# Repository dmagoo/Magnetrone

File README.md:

# Magnetrone

A motorized MIDI sequencer built around a rotating platter driven by a stepper motor.
Magnets placed on the platter pass over Hall effect sensors to trigger MIDI notes,
turning physical arrangement into musical pattern.

---

## Features

- Rotating platter driven by NEMA17 stepper via GT2 belt drive (11:1)
- 8 analog Hall effect sensors, one per note in the current scale
- MIDI note output on DIN connector
- Teensy Audio Shield output (headphone/line out) with a built-in synth and drum kit
- Voices: Piano, E. Piano, Organ, Synth, Bass, Strings, Brass, Mallets, Reed, Guitar
  and Drums, each with its own wave or harmonics, envelope, note length and filter,
  plus None to mute a layer
- Voice Edit (Aux): live tweaks to a layer's wave, envelope and note length,
  its first 16 harmonics, and its own filter with a filter envelope; Save As keeps them in Custom 1-8 (shared by all
  scenes) or as the current scene's own Scene Voice
- Edit Scale: a Custom scale with one chosen note per track, from Sound
  Defaults or live on the Aux; Save As keeps it in Custom 1-8 (shared by all
  scenes)
- Two magnet layers: a magnet's normal pole plays Layer A, its reversed pole Layer B
  (or both, with Layer B's Mode on Stack, or taking turns by revolution, with
  Layer Turns on Alternate, or each on its own Edit Turns pattern of up to 8
  revolutions),
  each with its own voice, MIDI channel, root note, scale, octave, level, Track
  Shift, Wrap and Low Note (Layer B can follow A's voice, octave, root, scale,
  shift and Low Note one by one, from the menu or the Aux; octave, root and
  scale follow by default)
- Per-layer effects, in a fixed chain: Tone (low-pass Cutoff and Resonance),
  Chorus (Rate, Depth, Mix), Delay (Sync to the beat or Free in ms, up to
  2.4 s, Feedback up to 90%, Mix) and Reverb (Room Size, Damping, Mix). Saved
  in scenes, all off by default; Layer B can follow A's per effect. Tone
  Cutoff, Delay Mix, Delay Feedback and Reverb Mix are also Aux Fns
- Per-layer Track Shift raises the run by scale degrees, with Wrap (the run
  rotates around the arm) or No Wrap (the whole run transposes)
- Per-layer Low Note: Inner or Outer sets which end of the sensor arm plays
  the low end of the run
- Drums play a fixed GM kit (one drum per track, busiest on the outer tracks) on
  MIDI channel 10; Track Shift rotates the kit around the tracks and Low Note
  Outer flips it end to end
- 1 revolution = 1 bar; BPM tracks RPM automatically. Beats/Rev from 1 to 32,
  platter speed from 1 to 120 RPM
- The platter is marked in 16 steps
- Bar start (StartPos): a start mark on the platter, located by calibration or
  re-found later (Auto from one magnet, or Manual by jogging the platter), and
  remembered across power cycles when the platter was at rest
- Front: where the player sits, set first in calibration and Calib. StartPos
  (the magnet is turned to the player, by hand or with the Speed knob, before
  the spin). Tools > Go to Front turns the mark there the shorter way round
- Placement Mode (Tools): Speed jogs the platter (press: Go to Front), Aux snaps
  to the next step or beat, Volume mutes and unmutes single tracks
- Scenes: the whole sound of both layers, 8 saved slots plus a Defaults scene
  edited from the menu; loaded live on the next bar start (or at once, Play
  Setup > Scene Load). Aux changes are live
  only, on top of the current scene. Read-only demo scenes are built into the
  firmware from JSON files (docs/scene-format.md), and a `scenes` serial
  command prints the saved scenes in that format
- Scene Codes (Aux > Scene Codes): a code of up to 14 characters for the
  current sound's main settings (each layer's root, octave, scale, voice,
  shift, Low Note, Wrap and mode, plus Layer Turns and the turn patterns), to enter on another
  table or after a firmware update. Fields at their defaults cost nothing, so
  a code changing only the roots is 3 characters
- [Record Designer](https://dmagoo.github.io/Magnetrone/tools/record-designer/) (`tools/record-designer/`): a
  browser tool to design a "record", a magnet pattern on a step grid plus its
  Scene Code, play it back, save songs and share them as links, and export a
  full-size SVG/PDF template to print or laser cut into a platter cover. Runs
  from the link or straight from disk
- MIDI beat clock driven by platter position, with Song Position Pointer so
  external bars line up with the start mark
- MIDI in (control only): a per-layer input channel; keys drive a MIDI Fn
  (Pitch, Shift, Scale Learn, Set Scale, Fingered or One Finger), the bend wheel bends the table, CC 7 volume,
  CC 20 octave; with Play Setup > MIDI CC on, CCs 74, 71, 93, 94, 12 and 91
  set the effects
- LCD menu: Sound Defaults (both layers), Play Setup, System and Tools
- Speed and volume adjustable live at any time via dedicated encoders; touching
  either one returns to the home screen from any menu (prompts and Scene
  Code entry excepted).
  From a stop, turning Speed starts from zero in the turned direction; a
  press resumes the last speed
- Aux knob changes one bound function live (Pitch, A/B Balance, Layer Turns, Load Scene,
  or a layer's Voice, Root Note, Scale, Octave, Shift, Low Note, Wrap, Mode,
  Tone Cutoff, Delay Mix, Delay Feedback or Reverb Mix); its list also holds
  Save Scene, Scene Codes and Reset All
- Menu knob opens the main menu from the home screen by turning or pressing;
  the Menu button leaves the Aux screens straight back to the home screen, and
  the Aux button leaves the main menu (prompts excepted)
- Welcome tune plays on boot -- previews what Layer A's tracks play, hall 1 to 8
  and back, including its key, octave, Track Shift, Wrap and Low Note; a Menu
  button press skips it
- LCD backlight timeout: configurable from always off to always on
- Stepper motor sleeps when idle to reduce heat and power draw
- Calibration (at 24 RPM, clear platter then one magnet on the start mark)
  measures sensor baselines and noise, threshold, magnet pole, the belt reduction
  (e.g. "Belt 10.9:1", counted in motor steps) and the bar start
- Tools menu: Go to StartPos, Go to Front, Placement Mode, calibration,
  StartPos, Machine Info (RPM, belt ratio, StartPos, threshold, motor driver), live
  Sensor Levels, Sensor Timing, Track Notes and Resources (audio load) screens, Reset Settings (keeps calibration, Front and scenes
  1-8) and Factory Reset
- All settings persisted to EEPROM across power cycles
- Teensy 4.1

---

## Code Summary

The firmware is structured as a set of independent modules: stepper motor control
uses an IntervalTimer ISR for non-blocking step generation; Hall sensor polling
fires each note when the magnet is centered on its sensor, predicted from a
threshold-to-peak angle each sensor learns as it plays (so timing holds on every
track and at any speed), with re-arm and debounce; the sequencer maps sensor
index to scale degree and fires timed MIDI note on/off pairs; the audio module drives
an 8-voice synth bank per magnet layer plus a shared drum kit through the SGTL5000
codec in parallel with MIDI out; the menu
is a simple state machine driven by three encoders with live speed and volume handling
at all times. The platter keeps a signed step count, so the bar phase is exact; MIDI
clock and scene loads are driven from it. A calibration routine samples the sensor
baselines and noise, counts motor steps over one platter revolution, and derives a threshold,
RPM correction factor and bar start stored in EEPROM.

---

## Hardware Summary

The controller is built on a Teensy 4.1 with a Teensy Audio Shield (SGTL5000) for
audio output. A NEMA17 stepper motor drives the platter through a GT2 belt at 11:1
reduction, controlled by a TMC2209 driver (configured over UART) from 24V DC. Eight
ratiometric Hall effect sensors (A1301) are powered at 3.3V and read directly by the
Teensy ADC. A 16x2 I2C LCD with PCF8574T backpack provides the display. MIDI DIN
in/out is present with optoisolation on the input. Power is supplied via 24V barrel
jack through a panel-mount power switch and an MP1584EN buck converter to 5V.

---

## Installation

### Requirements

- PlatformIO (CLI or VS Code extension)
- Teensy 4.1

### Build and Upload

1. Open the `firmware/` directory in VS Code with the PlatformIO extension,
   or use the PlatformIO CLI.

2. Build:

       cd firmware
       pio run -e teensy41

3. Upload:

       pio run -e teensy41 --target upload

### First Run

On first boot, no calibration data is present and the table offers to calibrate
(later: Menu > Tools > Full Calibrate). Clear the platter when asked, then place a
single magnet on the start mark on the outer track. See the
[user guide](docs/user-guide.md) for details.

### Diagnostics

For hardware faults, the firmware has a diagnostics mode used over the USB
serial monitor (`pio device monitor`). Hold the Menu button at power-up, or
type `diag` in the monitor while the table runs. It reports the display, audio
board, motor driver and every sensor every 5 seconds, and takes commands for
running and tuning the motor. Type `help` in the monitor for the commands; see
Troubleshooting > Diagnostics mode in the [user guide](docs/user-guide.md).

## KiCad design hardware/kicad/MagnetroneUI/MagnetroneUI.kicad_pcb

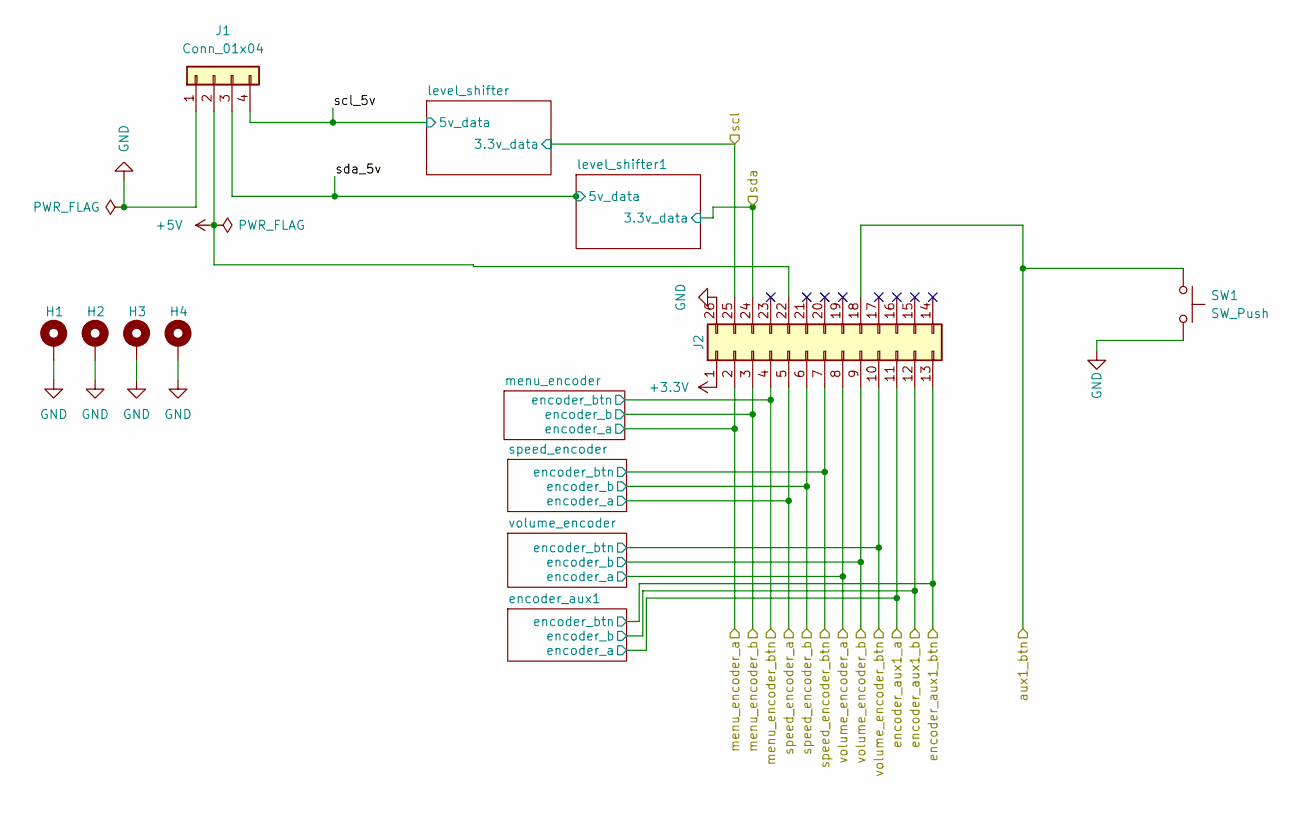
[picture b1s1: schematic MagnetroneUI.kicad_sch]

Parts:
H1, H2, H3, H4: MountingHole_Pad; MountingHole_3.2mm_M3_ISO7380_Pad_TopBottom
J1: Conn_01x04; PinHeader_1x04_P2.54mm_Vertical
J2: Conn_02x13_Counter_Clockwise; IDC-Header_2x13_P2.54mm_Horizontal
SW1: SW_Push; TerminalBlock_Phoenix_MKDS-1,5-2_1x02_P5.00mm_Horizontal

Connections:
+3.3V: J2.1; also elsewhere on the board
+5V: J1.2, J2.22; also elsewhere on the board
/aux1_btn: J2.18, SW1.1
/encoder_aux1_a: J2.11; also elsewhere on the board
/encoder_aux1_b: J2.12; also elsewhere on the board
/encoder_aux1_btn: J2.13; also elsewhere on the board
/menu_encoder_a: J2.2; also elsewhere on the board
/menu_encoder_b: J2.3; also elsewhere on the board
/menu_encoder_btn: J2.4; also elsewhere on the board
/scl: J2.25; also elsewhere on the board
/scl_5v: J1.4; also elsewhere on the board
/sda: J2.24; also elsewhere on the board
/sda_5v: J1.3; also elsewhere on the board
/speed_encoder_a: J2.5; also elsewhere on the board
/speed_encoder_b: J2.6; also elsewhere on the board
/speed_encoder_btn: J2.7; also elsewhere on the board
/volume_encoder_a: J2.8; also elsewhere on the board
/volume_encoder_b: J2.9; also elsewhere on the board
/volume_encoder_btn: J2.10; also elsewhere on the board
GND: H1.1, H2.1, H3.1, H4.1, J1.1, J2.26, SW1.2; also elsewhere on the board

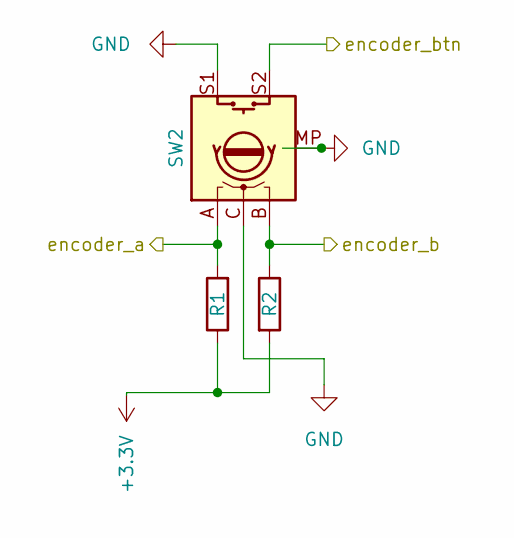
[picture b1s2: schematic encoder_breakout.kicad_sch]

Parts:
R1, R2: 10k; R_0805_2012Metric_Pad1.20x1.40mm_HandSolder
SW2: RotaryEncoder_Switch_MP; RotaryEncoder_Alps_EC11E-Switch_Vertical_H20mm

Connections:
+3.3V: R1.1, R2.2; also elsewhere on the board
/menu_encoder_a: R1.2, SW2.A; also elsewhere on the board
/menu_encoder_b: R2.1, SW2.B; also elsewhere on the board
/menu_encoder_btn: SW2.S2; also elsewhere on the board
GND: SW2.C, SW2.MP, SW2.S1; also elsewhere on the board

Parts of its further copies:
R3, R4, R5, R6, R7, R8: 10k; R_0805_2012Metric_Pad1.20x1.40mm_HandSolder
SW3, SW4, SW5: RotaryEncoder_Switch_MP; RotaryEncoder_Alps_EC11E-Switch_Vertical_H20mm

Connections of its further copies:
+3.3V: R3.1, R4.2, R5.1, R6.2, R7.1, R8.2; also elsewhere on the board
/encoder_aux1_a: R7.2, SW5.A; also elsewhere on the board
/encoder_aux1_b: R8.1, SW5.B; also elsewhere on the board
/encoder_aux1_btn: SW5.S2; also elsewhere on the board
/speed_encoder_a: R3.2, SW3.A; also elsewhere on the board
/speed_encoder_b: R4.1, SW3.B; also elsewhere on the board
/speed_encoder_btn: SW3.S2; also elsewhere on the board
/volume_encoder_a: R5.2, SW4.A; also elsewhere on the board
/volume_encoder_b: R6.1, SW4.B; also elsewhere on the board
/volume_encoder_btn: SW4.S2; also elsewhere on the board
GND: SW3.C, SW3.MP, SW3.S1, SW4.C, SW4.MP, SW4.S1, SW5.C, SW5.MP, SW5.S1; also elsewhere on the board

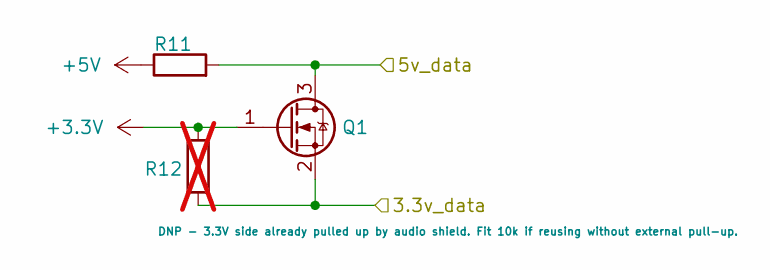
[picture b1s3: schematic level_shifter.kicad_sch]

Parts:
Q1: BSS138; SOT-23
R11: 10k; R_0805_2012Metric_Pad1.20x1.40mm_HandSolder
R12: 10k; R_0805_2012Metric_Pad1.20x1.40mm_HandSolder; not fitted

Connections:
+3.3V: Q1.1 (G), R12.1; also elsewhere on the board
+5V: R11.1; also elsewhere on the board
/scl: Q1.2 (S), R12.2; also elsewhere on the board
/scl_5v: Q1.3 (D), R11.2; also elsewhere on the board

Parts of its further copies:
Q2: BSS138; SOT-23
R13: 10k; R_0805_2012Metric_Pad1.20x1.40mm_HandSolder
R14: 10k; R_0805_2012Metric_Pad1.20x1.40mm_HandSolder; not fitted

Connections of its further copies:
+3.3V: Q2.1 (G), R14.1; also elsewhere on the board
+5V: R13.1; also elsewhere on the board
/sda: Q2.2 (S), R14.2; also elsewhere on the board
/sda_5v: Q2.3 (D), R13.2; also elsewhere on the board

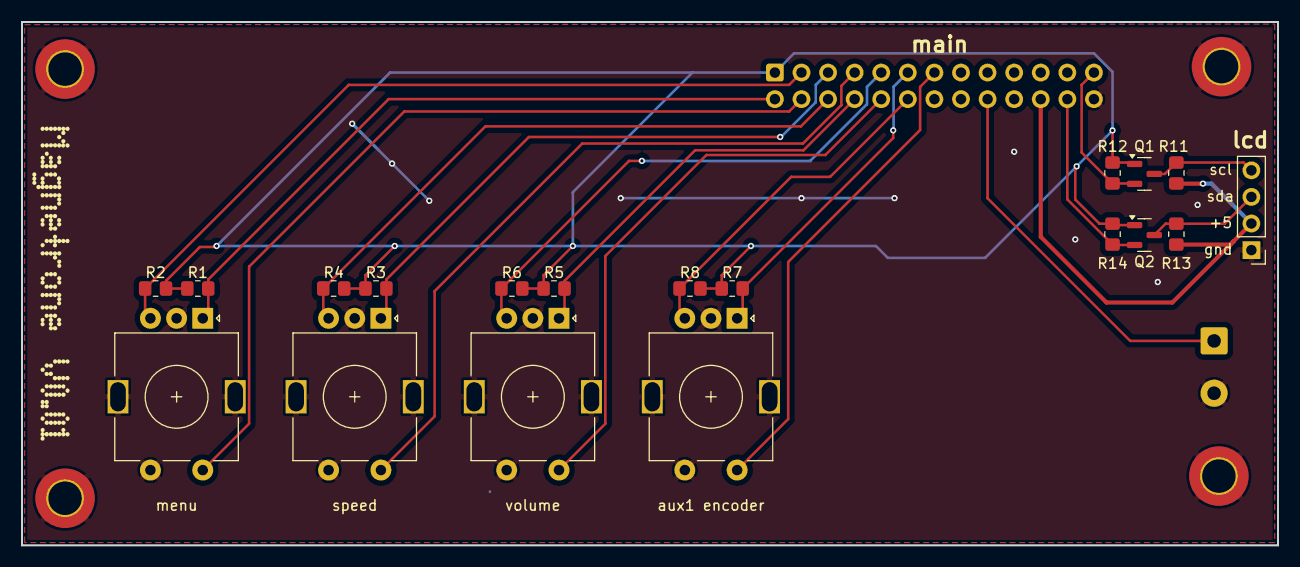
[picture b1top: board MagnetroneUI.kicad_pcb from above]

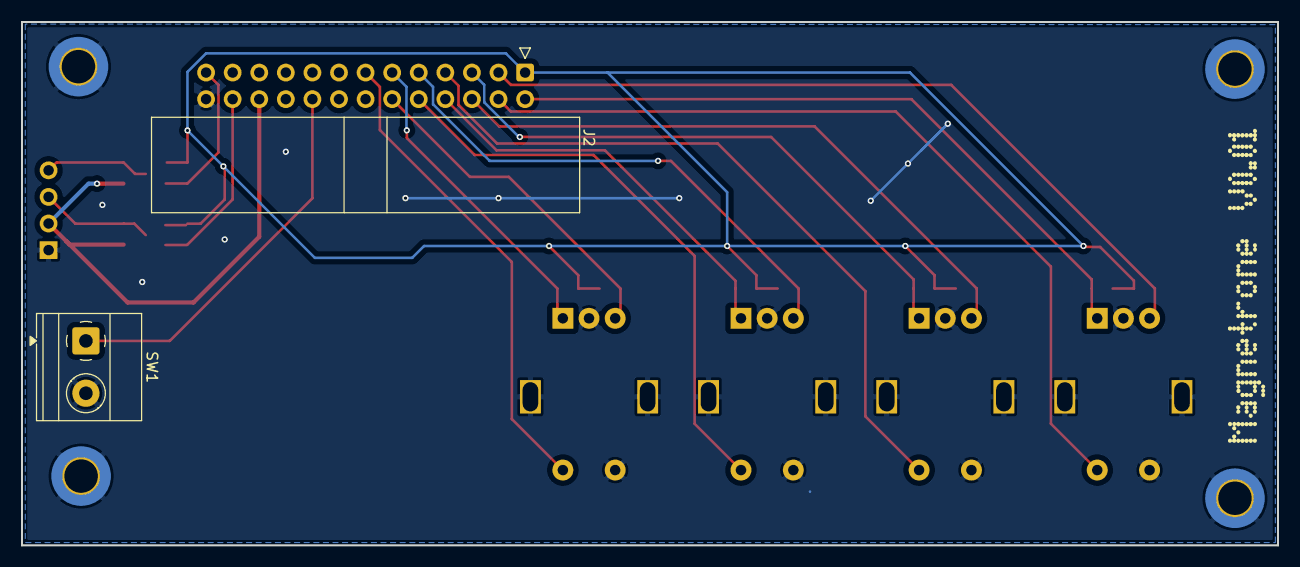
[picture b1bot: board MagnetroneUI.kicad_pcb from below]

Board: 2 copper layers, 120.0 x 50.0 mm, 25 parts (2 on the bottom side), 20 nets.

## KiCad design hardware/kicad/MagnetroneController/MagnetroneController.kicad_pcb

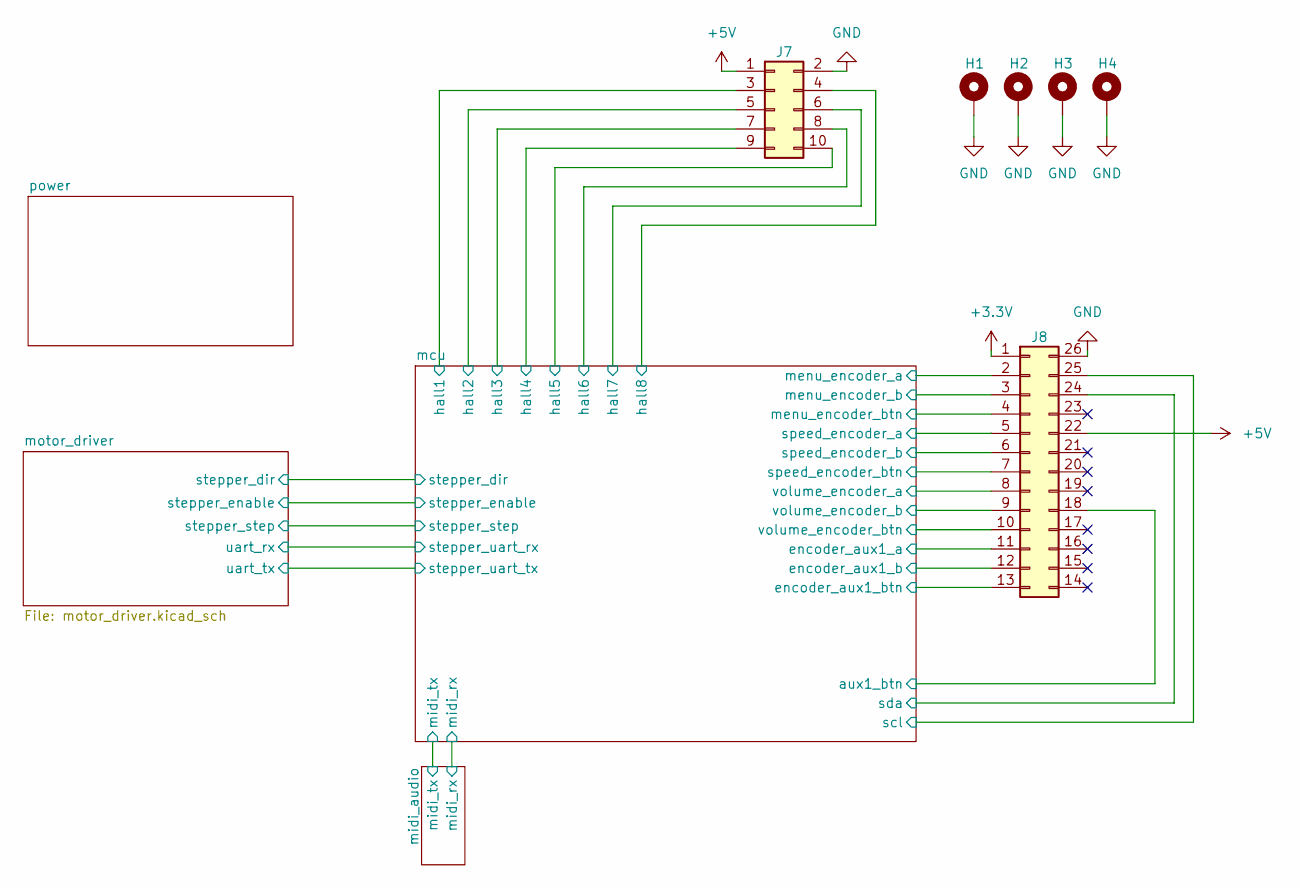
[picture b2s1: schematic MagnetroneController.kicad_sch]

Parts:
H1, H2, H3, H4: MountingHole_Pad; MountingHole_3.2mm_M3_ISO7380_Pad_TopBottom
J7: Conn_02x05_Odd_Even; IDC-Header_2x05_P2.54mm_Vertical
J8: Conn_02x13_Counter_Clockwise; IDC-Header_2x13_P2.54mm_Vertical

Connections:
+3.3V: J8.1; also elsewhere on the board
+5V: J7.1, J8.22; also elsewhere on the board
/mcu/aux1_btn: J8.18; also elsewhere on the board
/mcu/encoder_aux1_a: J8.11; also elsewhere on the board
/mcu/encoder_aux1_b: J8.12; also elsewhere on the board
/mcu/encoder_aux1_btn: J8.13; also elsewhere on the board
/mcu/hall1: J7.3; also elsewhere on the board
/mcu/hall2: J7.5; also elsewhere on the board
/mcu/hall3: J7.7; also elsewhere on the board
/mcu/hall4: J7.9; also elsewhere on the board
/mcu/hall5: J7.10; also elsewhere on the board
/mcu/hall6: J7.8; also elsewhere on the board
/mcu/hall7: J7.6; also elsewhere on the board
/mcu/hall8: J7.4; also elsewhere on the board
/mcu/menu_encoder_a: J8.2; also elsewhere on the board
/mcu/menu_encoder_b: J8.3; also elsewhere on the board
/mcu/menu_encoder_btn: J8.4; also elsewhere on the board
/mcu/scl: J8.25; also elsewhere on the board
/mcu/sda: J8.24; also elsewhere on the board
/mcu/speed_encoder_a: J8.5; also elsewhere on the board
/mcu/speed_encoder_b: J8.6; also elsewhere on the board
/mcu/speed_encoder_btn: J8.7; also elsewhere on the board
/mcu/volume_encoder_a: J8.8; also elsewhere on the board
/mcu/volume_encoder_b: J8.9; also elsewhere on the board
/mcu/volume_encoder_btn: J8.10; also elsewhere on the board
GND: H1.1, H2.1, H3.1, H4.1, J7.2, J8.26; also elsewhere on the board

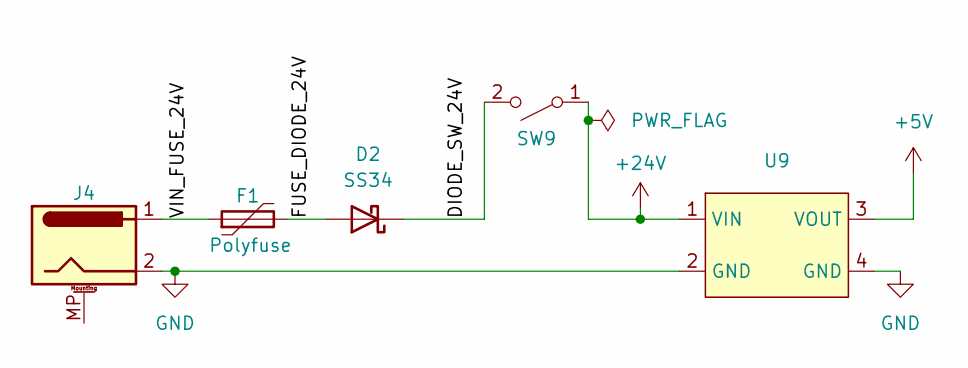
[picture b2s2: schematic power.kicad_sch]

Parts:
D2: SS34; D_SMA
F1: Polyfuse; Fuse_Bourns_MF-RHT300
J4: Barrel_Jack_MountingPin; BarrelJack_CUI_PJ-102AH_Horizontal
SW9: SW_SPST 24V; JST_XH_B2B-XH-AM_1x02_P2.50mm_Vertical
U9: SRT_MPT1584EN_Module

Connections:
+5V: U9.3 (VOUT); also elsewhere on the board
+24V: SW9.1 (A), U9.1 (VIN); also elsewhere on the board
/power/DIODE_SW_24V: D2.1 (K), SW9.2 (B)
/power/FUSE_DIODE_24V: D2.2 (A), F1.2
/power/VIN_FUSE_24V: F1.1, J4.1
GND: J4.2, U9.2 (GND), U9.4 (GND); also elsewhere on the board

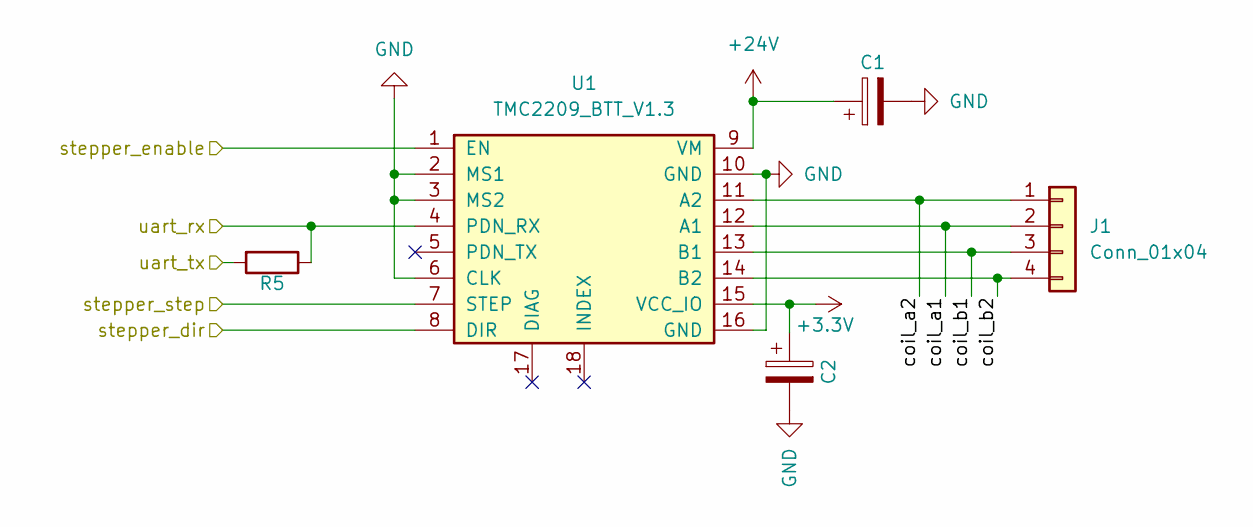
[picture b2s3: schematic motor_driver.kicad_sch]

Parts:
C1, C2: 100uf; CP_Radial_D8.0mm_P3.80mm
J1: Conn_01x04; PinHeader_1x04_P2.54mm_Vertical
R5: 1k; R_0805_2012Metric_Pad1.20x1.40mm_HandSolder
U1: TMC2209_BTT_V1.3

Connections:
+3.3V: C2.1, U1.15 (VCC_IO); also elsewhere on the board
+24V: C1.1, U1.9 (VM); also elsewhere on the board
/mcu/stepper_dir: U1.8 (DIR); also elsewhere on the board
/mcu/stepper_enable: U1.1 (EN); also elsewhere on the board
/mcu/stepper_step: U1.7 (STEP); also elsewhere on the board
/mcu/stepper_uart_rx: R5.1, U1.4 (PDN_RX); also elsewhere on the board
/mcu/stepper_uart_tx: R5.2; also elsewhere on the board
/motor_driver/coil_a1: J1.2, U1.12 (A1)
/motor_driver/coil_a2: J1.1, U1.11 (A2)
/motor_driver/coil_b1: J1.3, U1.13 (B1)
/motor_driver/coil_b2: J1.4, U1.14 (B2)
GND: C1.2, C2.2, U1.2 (MS1), U1.3 (MS2), U1.6 (CLK), U1.10 (GND), U1.16 (GND); also elsewhere on the board

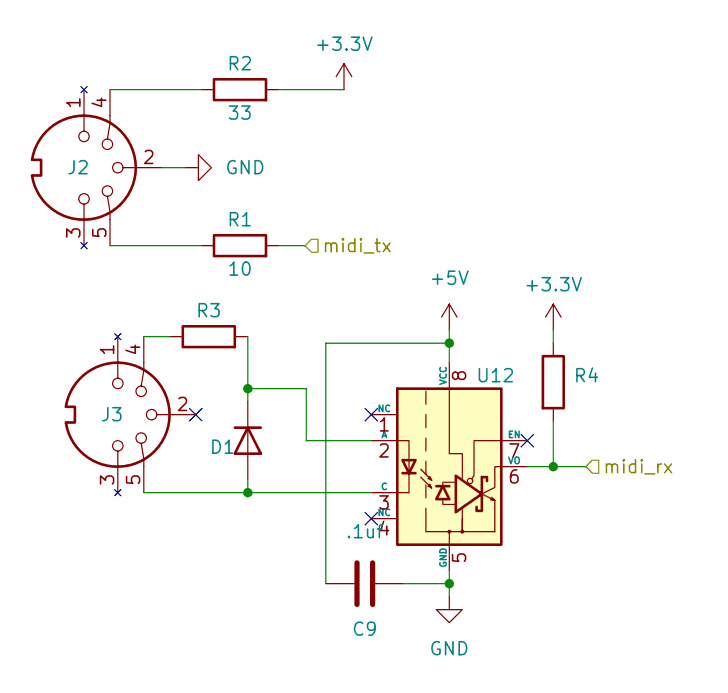
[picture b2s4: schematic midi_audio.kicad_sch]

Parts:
C9: .1uf; C_0805_2012Metric_Pad1.18x1.45mm_HandSolder
D1: D; D_SOD-123
J2, J3: DIN-5_180degree; MIDI_Wire_245
R1: 10; R_0805_2012Metric_Pad1.20x1.40mm_HandSolder
R2: 33; R_0805_2012Metric_Pad1.20x1.40mm_HandSolder
R3: 220; R_0805_2012Metric_Pad1.20x1.40mm_HandSolder
R4: 470; R_0805_2012Metric_Pad1.20x1.40mm_HandSolder
U12: 6N137; DIP-8_W7.62mm

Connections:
+3.3V: R2.2, R4.1; also elsewhere on the board
+5V: C9.2, U12.8 (VCC); also elsewhere on the board
/mcu/midi_rx: R4.2, U12.6 (VO); also elsewhere on the board
/mcu/midi_tx: R1.2; also elsewhere on the board
GND: C9.1, J2.2, U12.5 (GND); also elsewhere on the board
unnamed: D1.2 (A), J3.5, U12.3 (C)
unnamed: D1.1 (K), R3.2, U12.2 (A)
unnamed: J2.4, R2.1
unnamed: J2.5, R1.1
unnamed: J3.4, R3.1

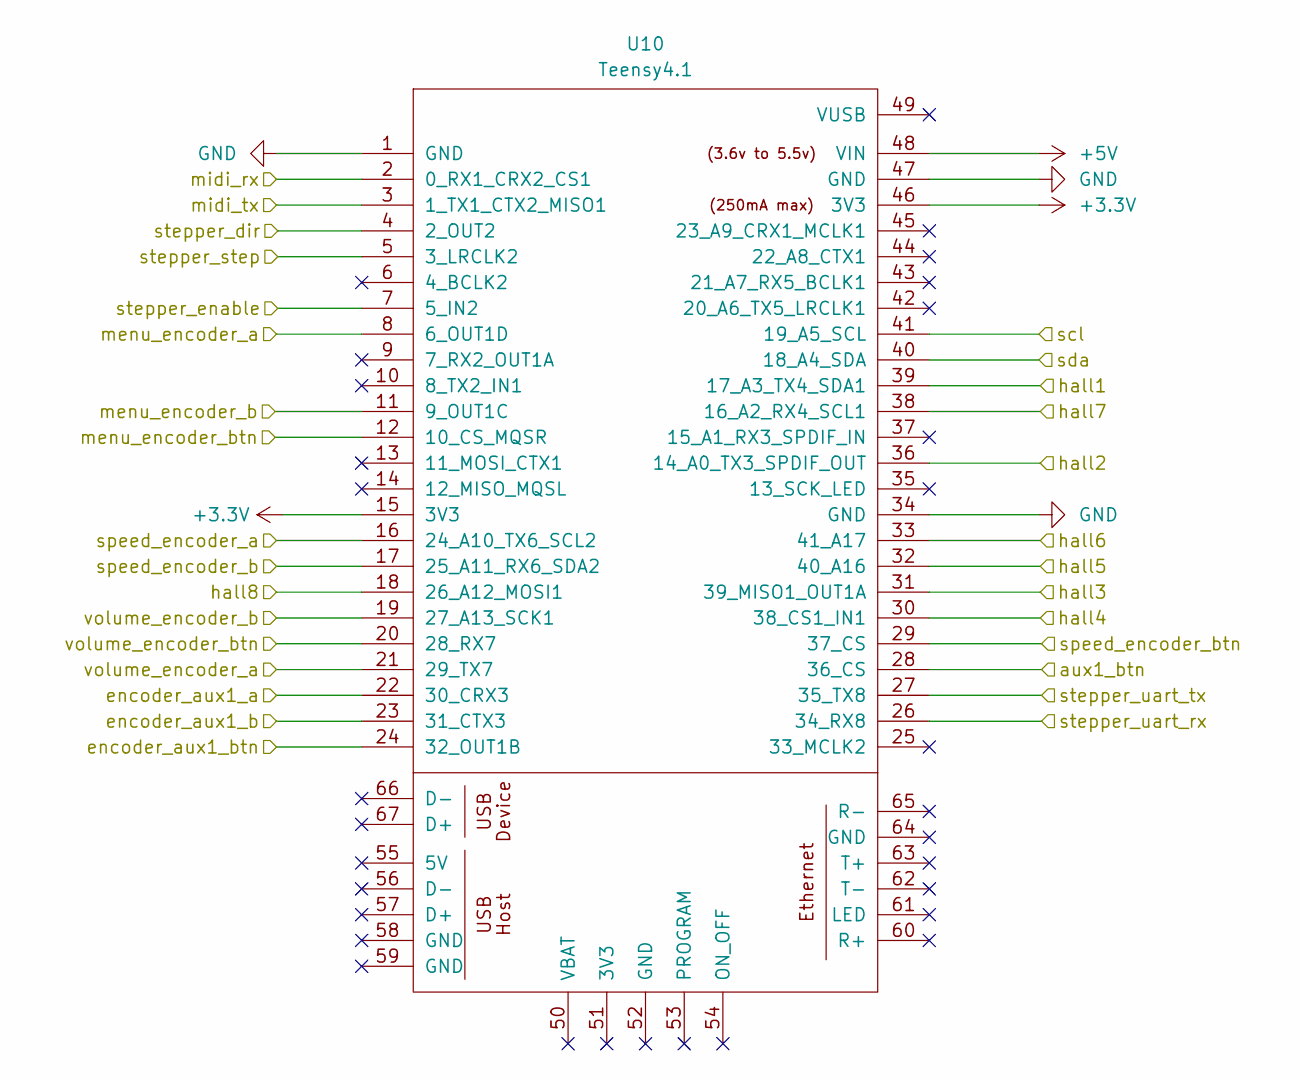
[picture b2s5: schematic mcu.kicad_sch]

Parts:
U10: Teensy4.1; Teensy41_AudioShield_RevD

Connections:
+3.3V: U10.15 (3V3), U10.46 (3V3); also elsewhere on the board
+5V: U10.48 (VIN); also elsewhere on the board
/mcu/aux1_btn: U10.28 (36_CS); also elsewhere on the board
/mcu/encoder_aux1_a: U10.22 (30_CRX3); also elsewhere on the board
/mcu/encoder_aux1_b: U10.23 (31_CTX3); also elsewhere on the board
/mcu/encoder_aux1_btn: U10.24 (32_OUT1B); also elsewhere on the board
/mcu/hall1: U10.39 (17_A3_TX4_SDA1); also elsewhere on the board
/mcu/hall2: U10.36 (14_A0_TX3_SPDIF_OUT); also elsewhere on the board
/mcu/hall3: U10.31 (39_MISO1_OUT1A); also elsewhere on the board
/mcu/hall4: U10.30 (38_CS1_IN1); also elsewhere on the board
/mcu/hall5: U10.32 (40_A16); also elsewhere on the board
/mcu/hall6: U10.33 (41_A17); also elsewhere on the board
/mcu/hall7: U10.38 (16_A2_RX4_SCL1); also elsewhere on the board
/mcu/hall8: U10.18 (26_A12_MOSI1); also elsewhere on the board
/mcu/menu_encoder_a: U10.8 (6_OUT1D); also elsewhere on the board
/mcu/menu_encoder_b: U10.11 (9_OUT1C); also elsewhere on the board
/mcu/menu_encoder_btn: U10.12 (10_CS_MQSR); also elsewhere on the board
/mcu/midi_rx: U10.2 (0_RX1_CRX2_CS1); also elsewhere on the board
/mcu/midi_tx: U10.3 (1_TX1_CTX2_MISO1); also elsewhere on the board
/mcu/scl: U10.41 (19_A5_SCL); also elsewhere on the board
/mcu/sda: U10.40 (18_A4_SDA); also elsewhere on the board
/mcu/speed_encoder_a: U10.16 (24_A10_TX6_SCL2); also elsewhere on the board
/mcu/speed_encoder_b: U10.17 (25_A11_RX6_SDA2); also elsewhere on the board
/mcu/speed_encoder_btn: U10.29 (37_CS); also elsewhere on the board
/mcu/stepper_dir: U10.4 (2_OUT2); also elsewhere on the board
/mcu/stepper_enable: U10.7 (5_IN2); also elsewhere on the board
/mcu/stepper_step: U10.5 (3_LRCLK2); also elsewhere on the board
/mcu/stepper_uart_rx: U10.26 (34_RX8); also elsewhere on the board
/mcu/stepper_uart_tx: U10.27 (35_TX8); also elsewhere on the board
/mcu/volume_encoder_a: U10.21 (29_TX7); also elsewhere on the board
/mcu/volume_encoder_b: U10.19 (27_A13_SCK1); also elsewhere on the board
/mcu/volume_encoder_btn: U10.20 (28_RX7); also elsewhere on the board
GND: U10.1 (GND), U10.34 (GND), U10.47 (GND); also elsewhere on the board

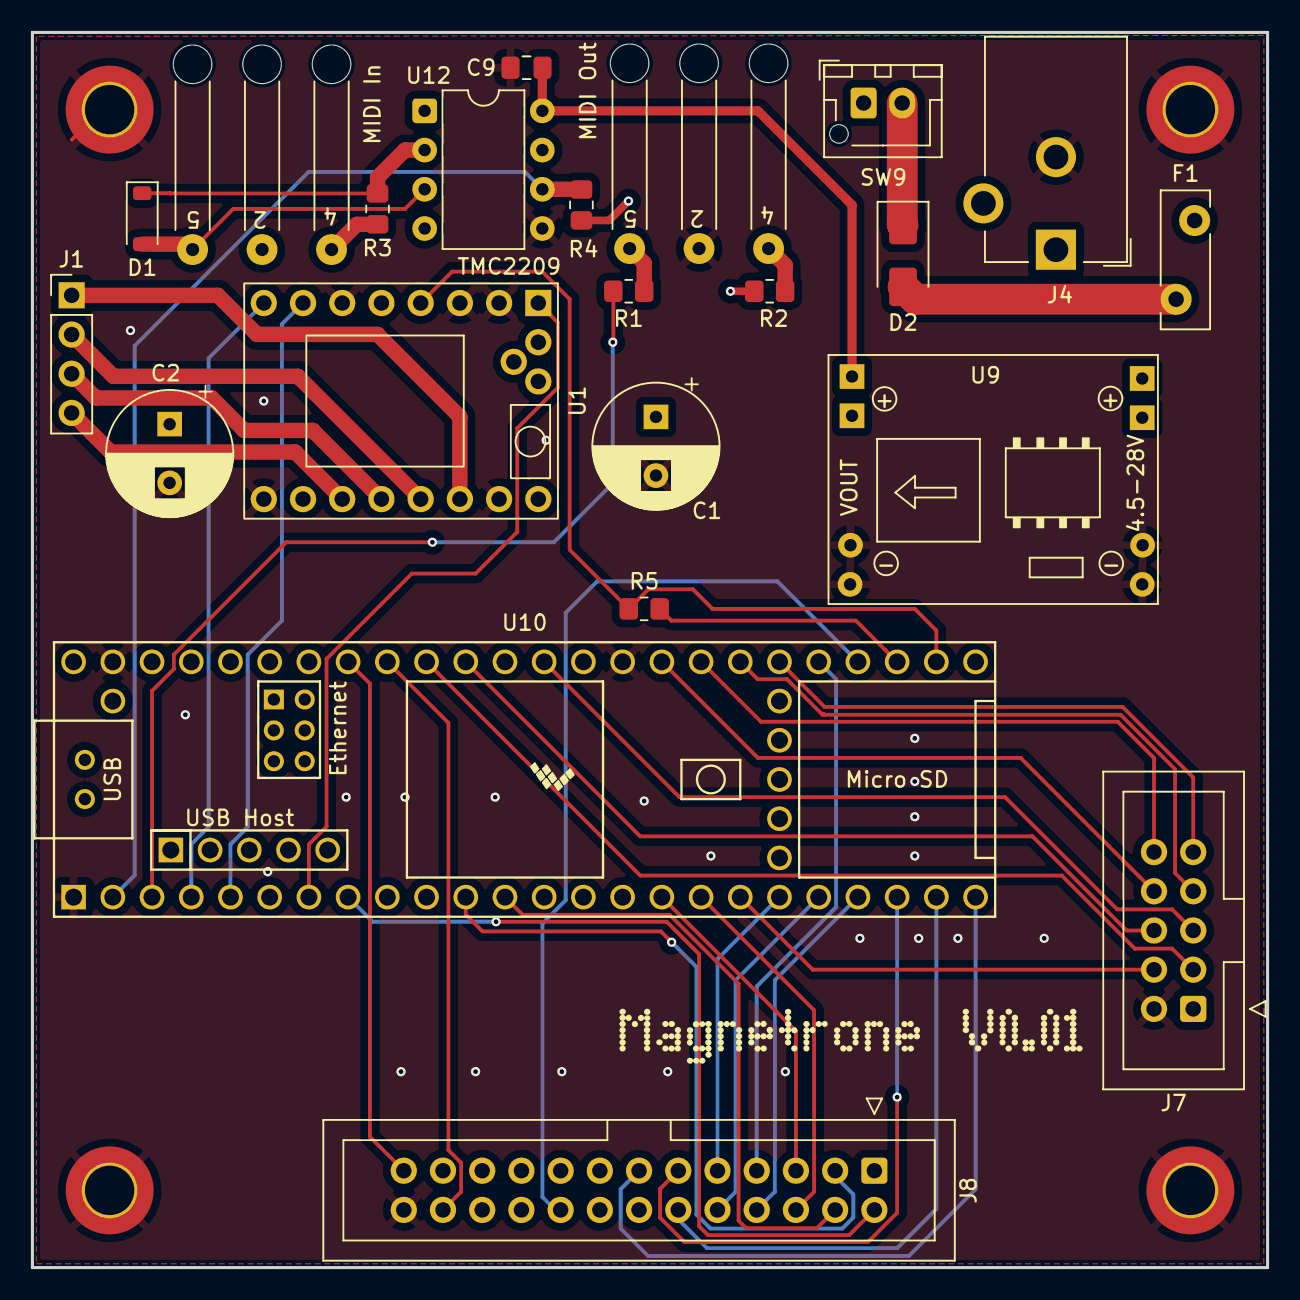
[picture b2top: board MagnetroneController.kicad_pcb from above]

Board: 4 copper layers, 80.0 x 80.0 mm, 26 parts (0 on the bottom side), 46 nets.

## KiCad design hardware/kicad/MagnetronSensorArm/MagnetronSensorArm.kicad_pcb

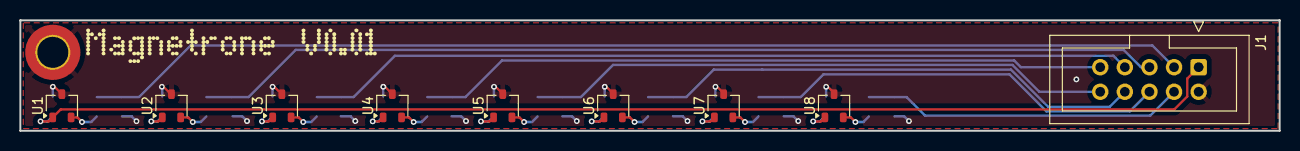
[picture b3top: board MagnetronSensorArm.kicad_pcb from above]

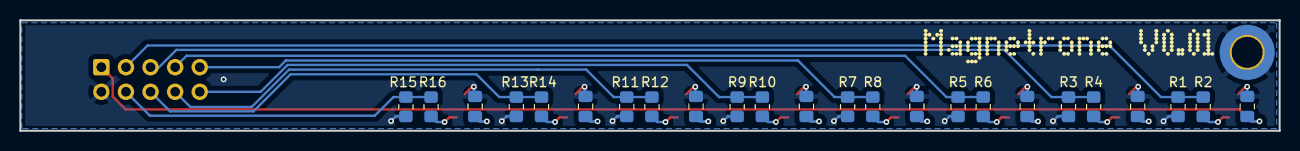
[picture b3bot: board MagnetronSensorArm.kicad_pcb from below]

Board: 4 copper layers, 130.0 x 11.4 mm, 34 parts (24 on the bottom side), 18 nets.

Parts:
C1, C2, C3, C4, C5, C6, C7, C8: .1uf; C_0805_2012Metric_Pad1.18x1.45mm_HandSolder
H1: MountingHole_Pad; MountingHole_3.2mm_M3_ISO7380_Pad_TopBottom
J1: Conn_02x05_Odd_Even; IDC-Header_2x05_P2.54mm_Vertical
R1, R3, R5, R7, R9, R11, R13, R15: 15k; R_0805_2012Metric_Pad1.20x1.40mm_HandSolder
R2, R4, R6, R8, R10, R12, R14, R16: 7.5k; R_0805_2012Metric_Pad1.20x1.40mm_HandSolder
U1, U2, U3, U4, U5, U6, U7, U8: A1301KLHLT-T; SOT-23W

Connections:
+5V: C1.1, C2.1, C3.1, C4.1, C5.1, C6.1, C7.1, C8.1, J1.1, U1.1 (VCC), U2.1 (VCC), U3.1 (VCC), U4.1 (VCC), U5.1 (VCC), U6.1 (VCC), U7.1 (VCC), U8.1 (VCC)
/hall1: J1.3, R1.2, R2.2
/hall2: J1.5, R3.2, R4.2
/hall3: J1.7, R5.2, R6.2
/hall4: J1.9, R7.2, R8.2
/hall5: J1.10, R9.2, R10.2
/hall6: J1.8, R11.2, R12.2
/hall7: J1.6, R13.2, R14.2
/hall8: J1.4, R15.2, R16.2
GND: C1.2, C2.2, C3.2, C4.2, C5.2, C6.2, C7.2, C8.2, H1.1, J1.2, R1.1, R3.1, R5.1, R7.1, R9.1, R11.1, R13.1, R15.1, U1.3 (GND), U2.3 (GND), U3.3 (GND), U4.3 (GND), U5.3 (GND), U6.3 (GND), U7.3 (GND), U8.3 (GND)
unnamed: R2.1, U1.2 (VOUT)
unnamed: R4.1, U2.2 (VOUT)
unnamed: R6.1, U3.2 (VOUT)
unnamed: R8.1, U4.2 (VOUT)
unnamed: R10.1, U5.2 (VOUT)
unnamed: R12.1, U6.2 (VOUT)
unnamed: R14.1, U7.2 (VOUT)
unnamed: R16.1, U8.2 (VOUT)
